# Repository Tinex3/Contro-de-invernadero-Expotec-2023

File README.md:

# Sistema de Control de Invernadero Expotec 2023

## Descripción

Este proyecto es un sistema de control de invernadero basado en control On-off. Utiliza tecnologías como LabVIEW 2013 y Arduino Firmware para proporcionar un control eficiente de las condiciones ambientales dentro del invernadero. La comunicación entre LabVIEW y Arduino se realiza a través de un puerto serial. Los valores de temperatura se pueden ajustar directamente en el código C++.

## Características Clave

- Control de temperatura y humedad en tiempo real.
- Interfaz de usuario amigable diseñada con LabVIEW 2013.
- Integración con sensores, incluyendo el sensor LM35DZ, DHT11 y el sensor de humedad YI-38, para un control preciso.
- Configuración personalizada de umbrales y alarmas a través del código de arduino.
- Control de dispositivos, como bomba y ventiladores, para mantener las condiciones ideales.

## Requisitos de Instalación

Para ejecutar este proyecto, necesitas:

- LabVIEW 2013.
- Arduino IDE (versión X.X.X)
- Hardware compatible con Arduino (sensores lm35DZ, DHT11 y sensor de humedad YI-38).
- Conexión física entre tu computadora y el Arduino a través de un puerto serial.
- NI Visa (versión 5.3) para la comunicación con LabVIEW.

## Instrucciones de Uso

1. Descarga y ejecuta la última versión del software.
2. Conecta los sensores y actuadores Arduino a tu invernadero.
3. Asegúrate de que la comunicación por puerto serial esté establecida entre LabVIEW y Arduino.
4. Abre la interfaz de usuario de LabVIEW 2013.
5. Configura los umbrales de temperatura y humedad directamente en el código CPP.
6. Inicia el sistema de control y monitorea las condiciones ambientales en tiempo real.
7. Controla dispositivos como la bomba y los ventiladores según sea necesario.

## Ejemplos y Escenarios de Uso

- Controla la temperatura y humedad en tu invernadero para el cultivo de plantas sensibles.
- Automatiza el riego y la ventilación en función de las condiciones actuales.
- Recibe alertas cuando se detecten condiciones fuera de los umbrales establecidos.

## Contribución y Desarrollo

Agradecemos las contribuciones de la comunidad. Si deseas contribuir a este proyecto, sigue los pasos a continuación:

1. Haz un fork del repositorio.
2. Crea una nueva rama para tu contribución.
3. Realiza los cambios y pruebas necesarios.
4. Envía una solicitud de extracción (pull request).

## Licencia

Este proyecto está bajo la [Licencia Apache 2.0](https://www.apache.org/licenses/LICENSE-2.0).

## Contacto y Soporte

Si tienes preguntas o necesitas asistencia, puedes contactarme en `b.riquelme.gomez@gmail.com`.

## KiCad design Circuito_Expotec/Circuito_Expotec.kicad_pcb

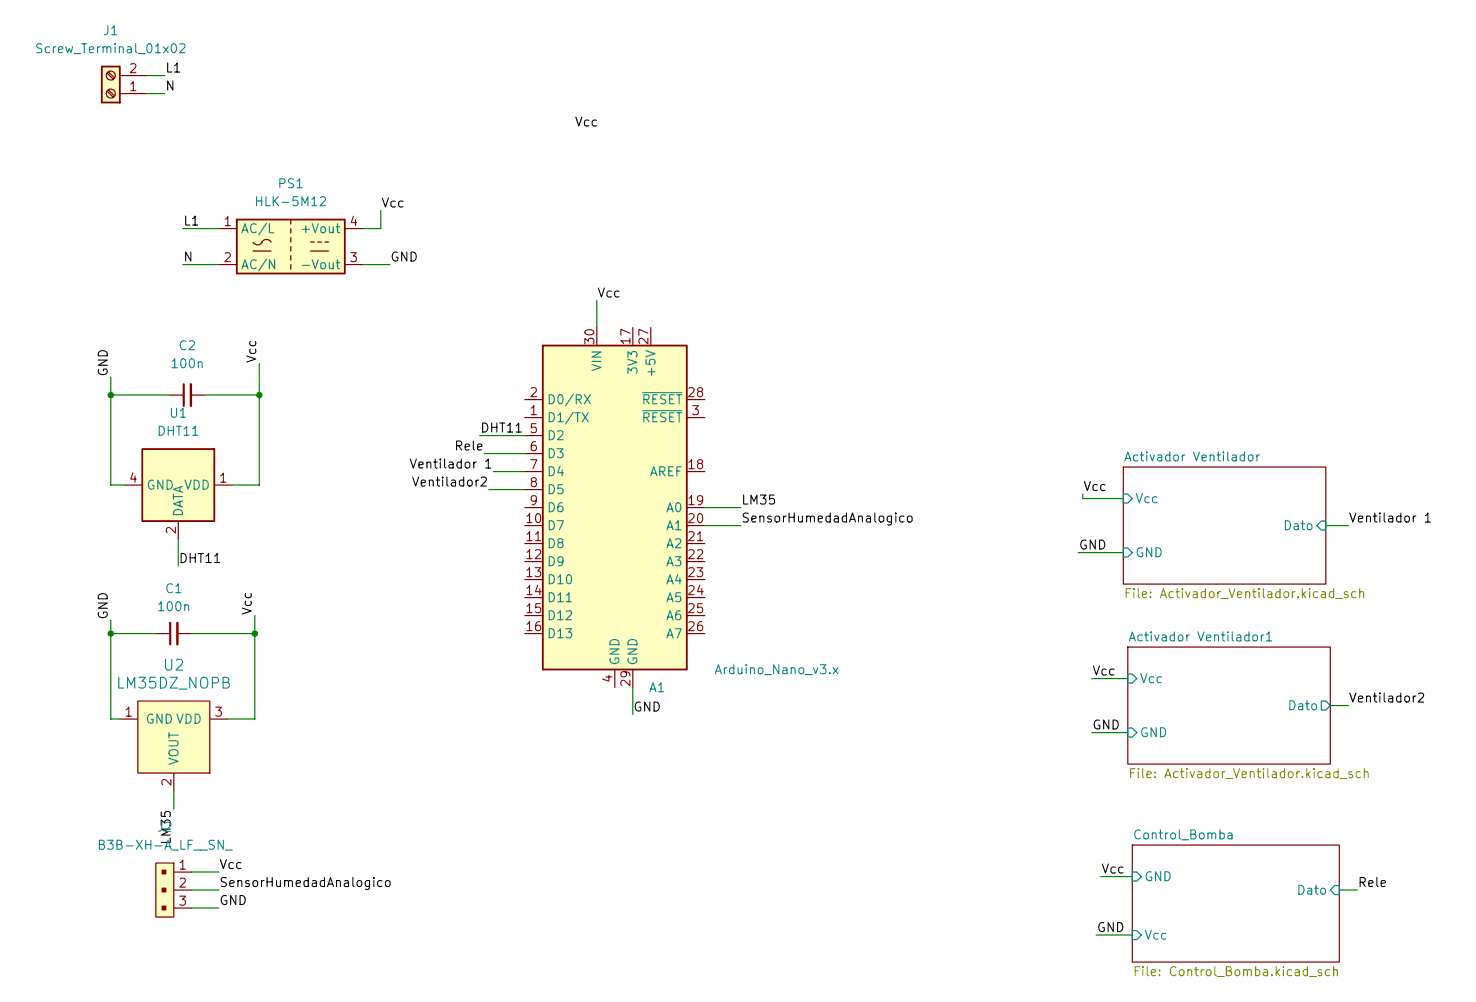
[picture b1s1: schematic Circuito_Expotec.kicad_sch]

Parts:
A1: Arduino_Nano_v3.x; Arduino_Nano
C1, C2: 100n; C_Disc_D6.0mm_W2.5mm_P5.00mm
J1: Screw_Terminal_01x02; TerminalBlock_MetzConnect_Type011_RT05502HBWC_1x02_P5.00mm_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
J2: B3B-XH-A_LF__SN_; PinHeader_1x3_P2.5mm_Drill1.1mm; MPN B3B-XH-A(LF)(SN); Digi-Key_PN 455-2248-ND
PS1: HLK-5M12; Converter_ACDC_HiLink_HLK-5Mxx
U1: DHT11; Aosong_DHT11_5.5x12.0_P2.54mm
U2: LM35DZ_NOPB; TO-92-3; MPN LM35DZ/NOPB; Digi-Key_PN LM35DZ/NOPB-ND

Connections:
/DHT11: A1.5 (D2), U1.2 (DATA)
/GND: A1.29 (GND), C1.1, C2.1, J2.3, PS1.3 (-Vout), U1.4 (GND), U2.1 (GND); also elsewhere on the board
/L1: J1.2, PS1.1 (AC/L)
/LM35: A1.19 (A0), U2.2 (VOUT)
/N: J1.1, PS1.2 (AC/N)
/Rele: A1.6 (D3); also elsewhere on the board
/SensorHumedadAnalogico: A1.20 (A1), J2.2
/Vcc: A1.30 (VIN), C1.2, C2.2, J2.1, PS1.4 (+Vout), U1.1 (VDD), U2.3 (VDD); also elsewhere on the board
/Ventilador2: A1.8 (D5); also elsewhere on the board
/Ventilador 1: A1.7 (D4); also elsewhere on the board

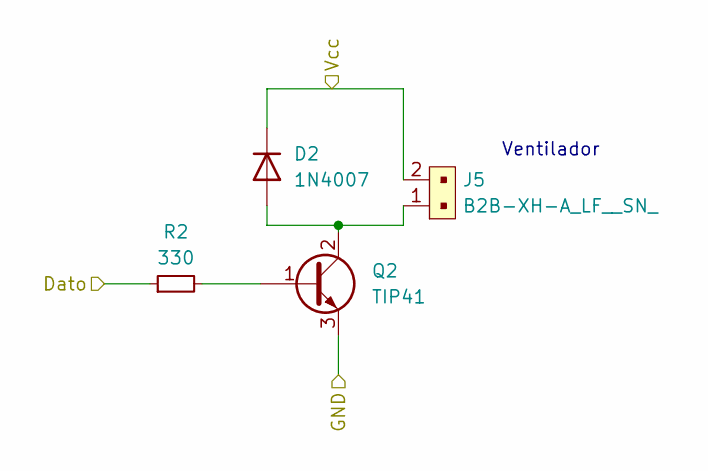
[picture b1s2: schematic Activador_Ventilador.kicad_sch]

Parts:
D2: 1N4007; D_DO-41_SOD81_P10.16mm_Horizontal
J5: B2B-XH-A_LF__SN_; PinHeader_1x2_P2.5mm_Drill1.1mm; MPN B2B-XH-A(LF)(SN); Digi-Key_PN 455-2247-ND
Q2: TIP41; TO-220-3_Vertical
R2: 330; R_1206_3216Metric

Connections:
/GND: Q2.3 (E); also elsewhere on the board
/Vcc: D2.1 (K), J5.2; also elsewhere on the board
/Ventilador2: R2.1; also elsewhere on the board
unnamed: D2.2 (A), J5.1, Q2.2 (C)
unnamed: Q2.1 (B), R2.2

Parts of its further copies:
D1: 1N4007; D_DO-41_SOD81_P10.16mm_Horizontal
J3: B2B-XH-A_LF__SN_; PinHeader_1x2_P2.5mm_Drill1.1mm; MPN B2B-XH-A(LF)(SN); Digi-Key_PN 455-2247-ND
Q1: TIP41; TO-220-3_Vertical
R1: 330; R_1206_3216Metric

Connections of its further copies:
/GND: Q1.3 (E); also elsewhere on the board
/Vcc: D1.1 (K), J3.2; also elsewhere on the board
/Ventilador 1: R1.1; also elsewhere on the board
unnamed: D1.2 (A), J3.1, Q1.2 (C)
unnamed: Q1.1 (B), R1.2

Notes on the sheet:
Ventilador

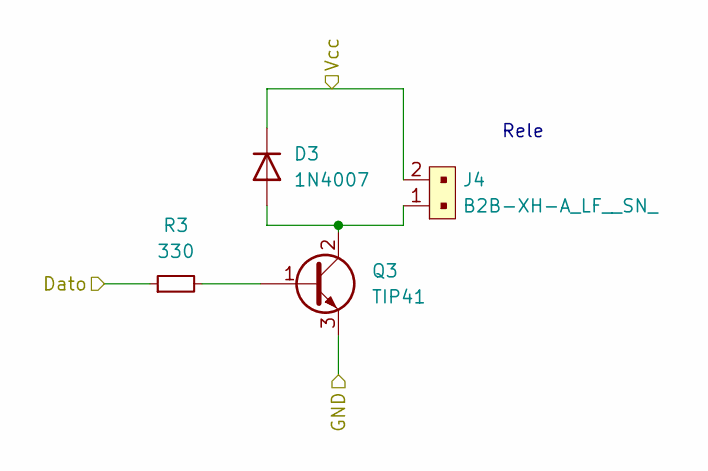
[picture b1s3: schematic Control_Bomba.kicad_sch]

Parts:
D3: 1N4007; D_DO-41_SOD81_P10.16mm_Horizontal
J4: B2B-XH-A_LF__SN_; PinHeader_1x2_P2.5mm_Drill1.1mm; MPN B2B-XH-A(LF)(SN); Digi-Key_PN 455-2247-ND
Q3: TIP41; TO-220-3_Vertical
R3: 330; R_1206_3216Metric

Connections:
/GND: D3.1 (K), J4.2; also elsewhere on the board
/Rele: R3.1; also elsewhere on the board
/Vcc: Q3.3 (E); also elsewhere on the board
unnamed: D3.2 (A), J4.1, Q3.2 (C)
unnamed: Q3.1 (B), R3.2

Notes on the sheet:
Rele

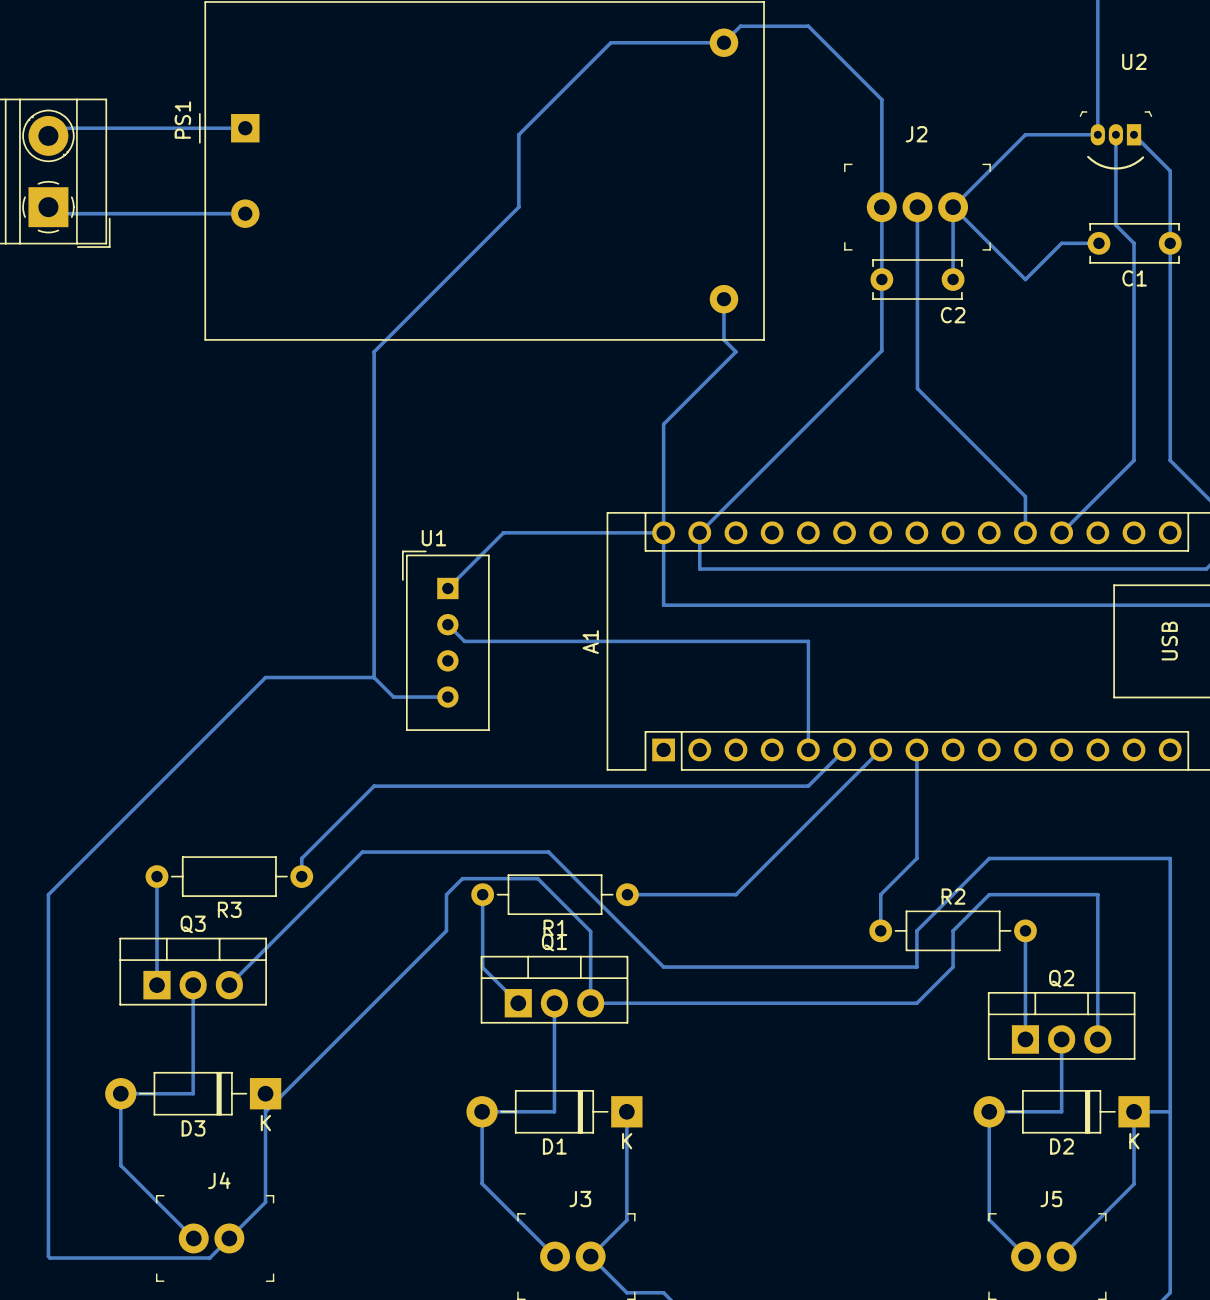
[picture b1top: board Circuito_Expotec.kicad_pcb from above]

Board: 2 copper layers, 20 parts (0 on the bottom side), 16 nets.

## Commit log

2023-09-22 Archivos nuevos! :D
2023-09-22 Fix PlatformIO
2023-10-09 Upgrade 1.2.0
2024-01-20 Se corrigen nombre de sensor de temperatura
2024-01-20 Se agrega extructura de datos
2024-01-20 Se crea circuito en kicad
2024-01-23 Se guardan cambios
